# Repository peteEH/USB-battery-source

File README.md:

# USB-battery-source
USB Mini to 4 outputs using linear regulator - set for 1.5V (NiMH or AA battery source)

## LICENSE ##
Hardware License is Creative Commons - Attribution 3.0

Feel free to use these files to learn, explore electronics.

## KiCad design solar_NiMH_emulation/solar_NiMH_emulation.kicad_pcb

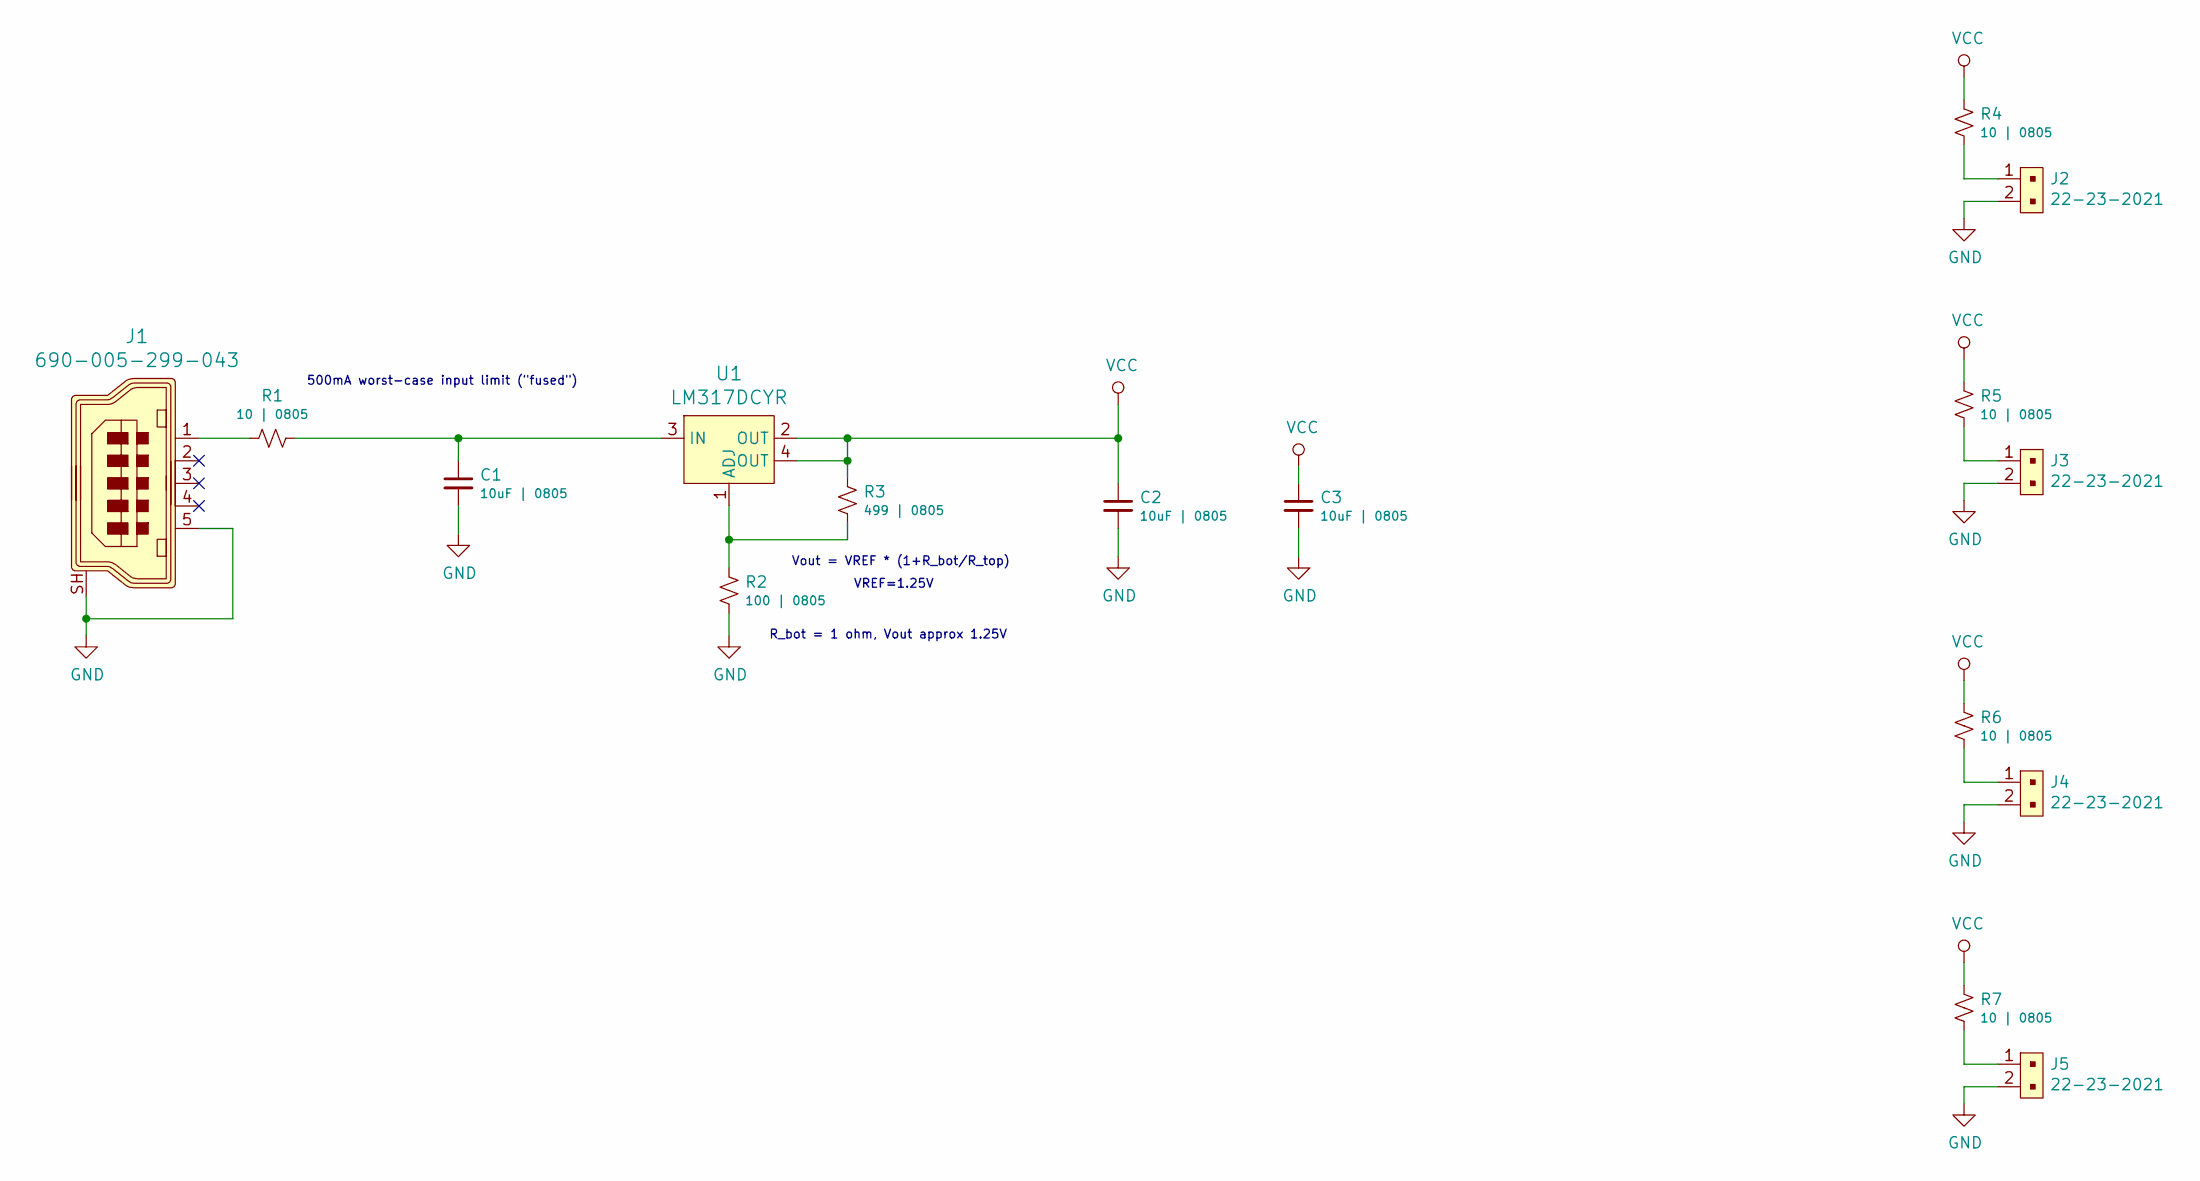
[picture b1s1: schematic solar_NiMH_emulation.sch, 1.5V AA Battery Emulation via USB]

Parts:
C1, C2, C3: 10uF | 0805; C_0805_2012Metric
J1: 690-005-299-043; USB_Mini_B_Female_690-005-299-043; MPN 690-005-299-043; Digi-Key_PN 151-1206-1-ND
J2, J3, J4, J5: 22-23-2021; PinHeader_1x2_P2.54mm_Drill1.02mm; MPN 22-23-2021; Digi-Key_PN WM4200-ND
R1, R4, R5, R6, R7: 10 | 0805; R_0805_2012Metric
R2: 100 | 0805; R_0805_2012Metric
R3: 499 | 0805; R_0805_2012Metric
U1: LM317DCYR; SOT-223-4; MPN LM317DCYR; Digi-Key_PN 296-12602-1-ND

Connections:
GND: C1.2, C2.2, C3.2, J1.5, J1.SH, J2.2, J3.2, J4.2, J5.2, R2.2
unnamed: C1.1, R1.1, U1.3 (IN)
unnamed: J1.1, R1.2
unnamed: J2.1, R4.2
unnamed: J3.1, R5.2
unnamed: J4.1, R6.2
unnamed: J5.1, R7.2
unnamed: R2.1, R3.2, U1.1 (ADJ)
VCC: C2.1, C3.1, R3.1, R4.1, R5.1, R6.1, R7.1, U1.2 (OUT), U1.4 (OUT)

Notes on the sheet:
Vout = VREF * (1+R_bot/R_top)
VREF=1.25V
R_bot = 1 ohm, Vout approx 1.25V
500mA worst-case input limit ("fused")

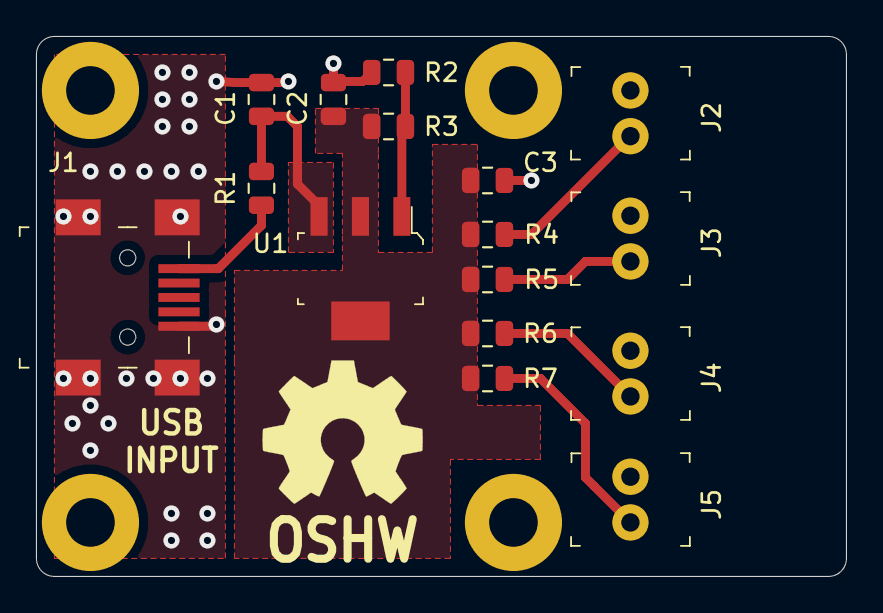
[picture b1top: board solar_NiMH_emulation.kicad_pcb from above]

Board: 2 copper layers, 45.0 x 30.0 mm, 16 parts (0 on the bottom side), 9 nets.

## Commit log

2019-10-26 initial set of files
2019-10-26 license add
